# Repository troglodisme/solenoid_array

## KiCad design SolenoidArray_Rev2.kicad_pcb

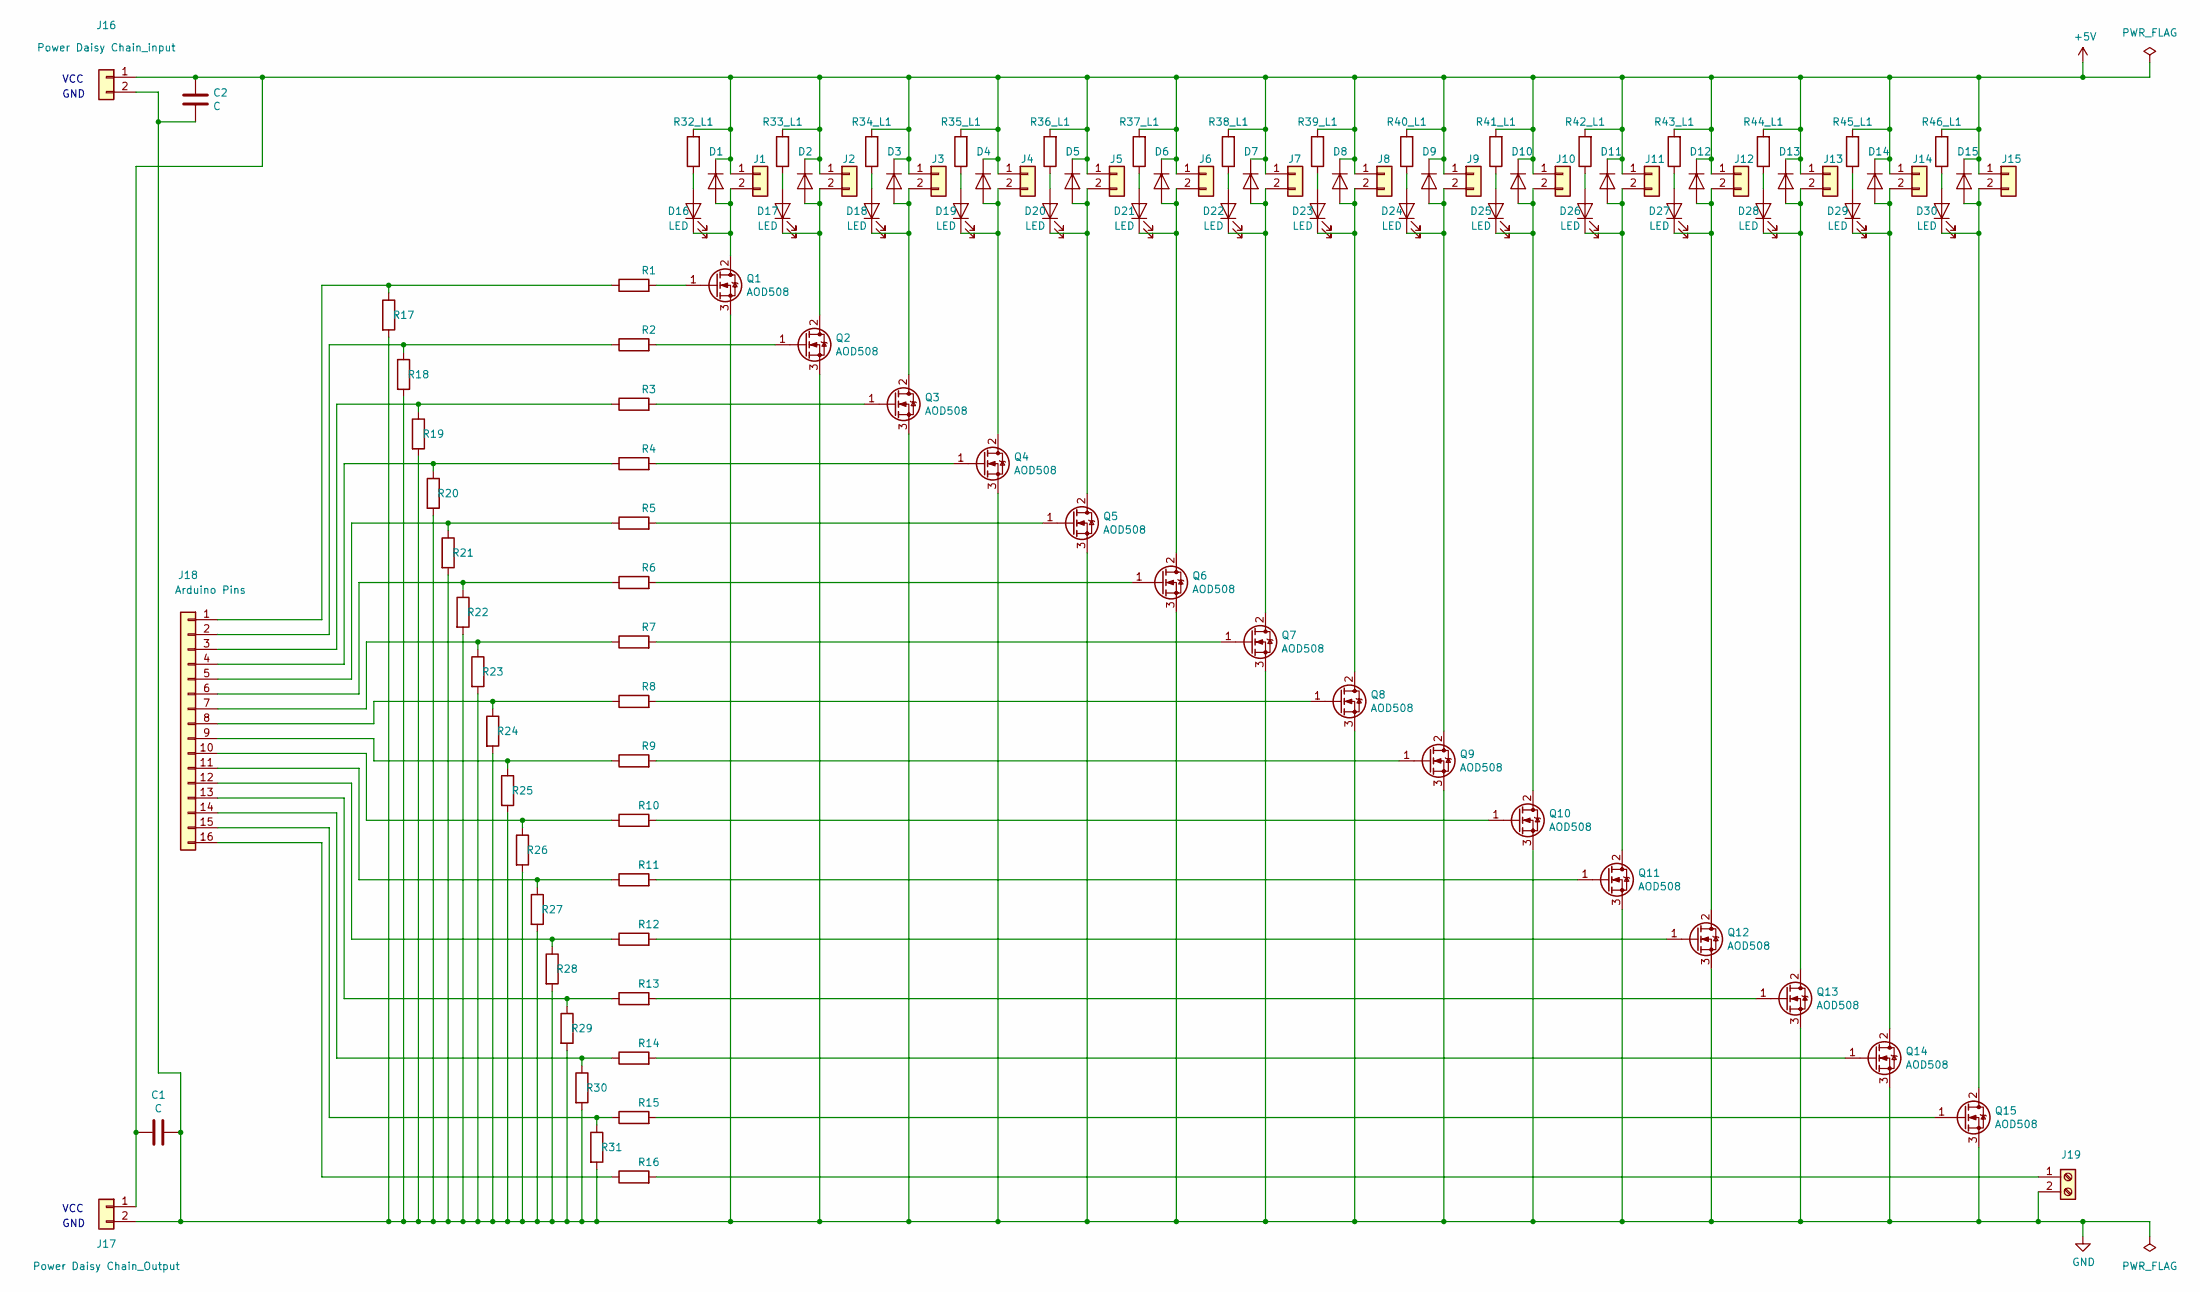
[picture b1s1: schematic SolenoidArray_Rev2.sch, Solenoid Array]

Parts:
C1, C2: C; C_1210_3225Metric_Pad1.42x2.65mm_HandSolder
D1, D2, D3, D4, D5, D6, D7, D8, D9, D10, D11, D12, D13, D14, D15: 1N4004; D_1210_3225Metric_Pad1.42x2.65mm_HandSolder
D16, D17, D18, D19, D20, D21, D22, D23, D24, D25, D26, D27, D28, D29, D30: LED; LED_1210_3225Metric_Pad1.42x2.65mm_HandSolder
J1, J2, J3, J4, J5, J6, J7, J8, J9, J10, J11, J12, J13, J14, J15: Conn_01x02; JST_PH_S2B-PH-K_1x02_P2.00mm_Horizontal
J16: Power Daisy Chain_input; JST_PH_S2B-PH-K_1x02_P2.00mm_Horizontal
J17: Power Daisy Chain_Output; JST_PH_S2B-PH-K_1x02_P2.00mm_Horizontal
J18: Arduino Pins; IDC-Header_2x08_P2.54mm_Vertical
J19: Screw_Terminal_01x02; TerminalBlock_TE_282834-2_1x02_P2.54mm_Horizontal
Q1, Q2, Q3, Q4, Q5, Q6, Q7, Q8, Q9, Q10, Q11, Q12, Q13, Q14, Q15: AOD508; TO252 (DPAK)
R1, R2, R3, R4, R5, R6, R7, R8, R9, R10, R11, R12, R13, R14, R15, R16, R17, R18, R19, R20, R21, R22, R23, R24, R25, R26, R27, R28, R29, R30, R31, R32_L1, R33_L1, R34_L1, R35_L1, R36_L1, R37_L1, R38_L1, R39_L1, R40_L1, R41_L1, R42_L1, R43_L1, R44_L1, R45_L1, R46_L1: R; R_1210_3225Metric_Pad1.42x2.65mm_HandSolder

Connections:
+5V: C1.2, C2.2, D1.1 (K), D2.1 (K), D3.1 (K), D4.1 (K), D5.1 (K), D6.1 (K), D7.1 (K), D8.1 (K), D9.1 (K), D10.1 (K), D11.1 (K), D12.1 (K), D13.1 (K), D14.1 (K), D15.1 (K), J1.1, J2.1, J3.1, J4.1, J5.1, J6.1, J7.1, J8.1, J9.1, J10.1, J11.1, J12.1, J13.1, J14.1, J15.1, J16.1, J17.1, R32_L1.2, R33_L1.2, R34_L1.2, R35_L1.2, R36_L1.2, R37_L1.2, R38_L1.2, R39_L1.2, R40_L1.2, R41_L1.2, R42_L1.2, R43_L1.2, R44_L1.2, R45_L1.2, R46_L1.2
GND: C1.1, C2.1, J16.2, J17.2, J19.2, Q1.3 (S), Q2.3 (S), Q3.3 (S), Q4.3 (S), Q5.3 (S), Q6.3 (S), Q7.3 (S), Q8.3 (S), Q9.3 (S), Q10.3 (S), Q11.3 (S), Q12.3 (S), Q13.3 (S), Q14.3 (S), Q15.3 (S), R17.2, R18.2, R19.2, R20.2, R21.2, R22.2, R23.2, R24.2, R25.2, R26.2, R27.2, R28.2, R29.2, R30.2, R31.2
unnamed: D1.2 (A), D16.1 (K), J1.2, Q1.2 (D)
unnamed: D10.2 (A), D25.1 (K), J10.2, Q10.2 (D)
unnamed: D11.2 (A), D26.1 (K), J11.2, Q11.2 (D)
unnamed: D12.2 (A), D27.1 (K), J12.2, Q12.2 (D)
unnamed: D13.2 (A), D28.1 (K), J13.2, Q13.2 (D)
unnamed: D14.2 (A), D29.1 (K), J14.2, Q14.2 (D)
unnamed: D15.2 (A), D30.1 (K), J15.2, Q15.2 (D)
unnamed: D16.2 (A), R32_L1.1
unnamed: D2.2 (A), D17.1 (K), J2.2, Q2.2 (D)
unnamed: D17.2 (A), R33_L1.1
unnamed: D3.2 (A), D18.1 (K), J3.2, Q3.2 (D)
unnamed: D18.2 (A), R34_L1.1
unnamed: D4.2 (A), D19.1 (K), J4.2, Q4.2 (D)
unnamed: D19.2 (A), R35_L1.1
unnamed: D5.2 (A), D20.1 (K), J5.2, Q5.2 (D)
unnamed: D20.2 (A), R36_L1.1
unnamed: D6.2 (A), D21.1 (K), J6.2, Q6.2 (D)
unnamed: D21.2 (A), R37_L1.1
unnamed: D7.2 (A), D22.1 (K), J7.2, Q7.2 (D)
unnamed: D22.2 (A), R38_L1.1
unnamed: D8.2 (A), D23.1 (K), J8.2, Q8.2 (D)
unnamed: D23.2 (A), R39_L1.1
unnamed: D9.2 (A), D24.1 (K), J9.2, Q9.2 (D)
unnamed: D24.2 (A), R40_L1.1
unnamed: D25.2 (A), R41_L1.1
unnamed: D26.2 (A), R42_L1.1
unnamed: D27.2 (A), R43_L1.1
unnamed: D28.2 (A), R44_L1.1
unnamed: D29.2 (A), R45_L1.1
unnamed: D30.2 (A), R46_L1.1
unnamed: J18.1, R1.1, R17.1
unnamed: J18.2, R2.1, R18.1
unnamed: J18.3, R3.1, R19.1
unnamed: J18.4, R4.1, R20.1
unnamed: J18.5, R5.1, R21.1
unnamed: J18.6, R6.1, R22.1
unnamed: J18.7, R7.1, R23.1
unnamed: J18.8, R8.1, R24.1
unnamed: J18.9, R9.1, R25.1
unnamed: J18.10, R10.1, R26.1
unnamed: J18.11, R11.1, R27.1
unnamed: J18.12, R12.1, R28.1
unnamed: J18.13, R13.1, R29.1
unnamed: J18.14, R14.1, R30.1
unnamed: J18.15, R15.1, R31.1
unnamed: J18.16, R16.1
unnamed: J19.1, R16.2
unnamed: Q1.1 (G), R1.2
unnamed: Q2.1 (G), R2.2
unnamed: Q3.1 (G), R3.2
unnamed: Q4.1 (G), R4.2
unnamed: Q5.1 (G), R5.2
unnamed: Q6.1 (G), R6.2
unnamed: Q7.1 (G), R7.2
unnamed: Q8.1 (G), R8.2
unnamed: Q9.1 (G), R9.2
unnamed: Q10.1 (G), R10.2
unnamed: Q11.1 (G), R11.2
unnamed: Q12.1 (G), R12.2
unnamed: Q13.1 (G), R13.2
unnamed: Q14.1 (G), R14.2
unnamed: Q15.1 (G), R15.2

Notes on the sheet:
GND
VCC

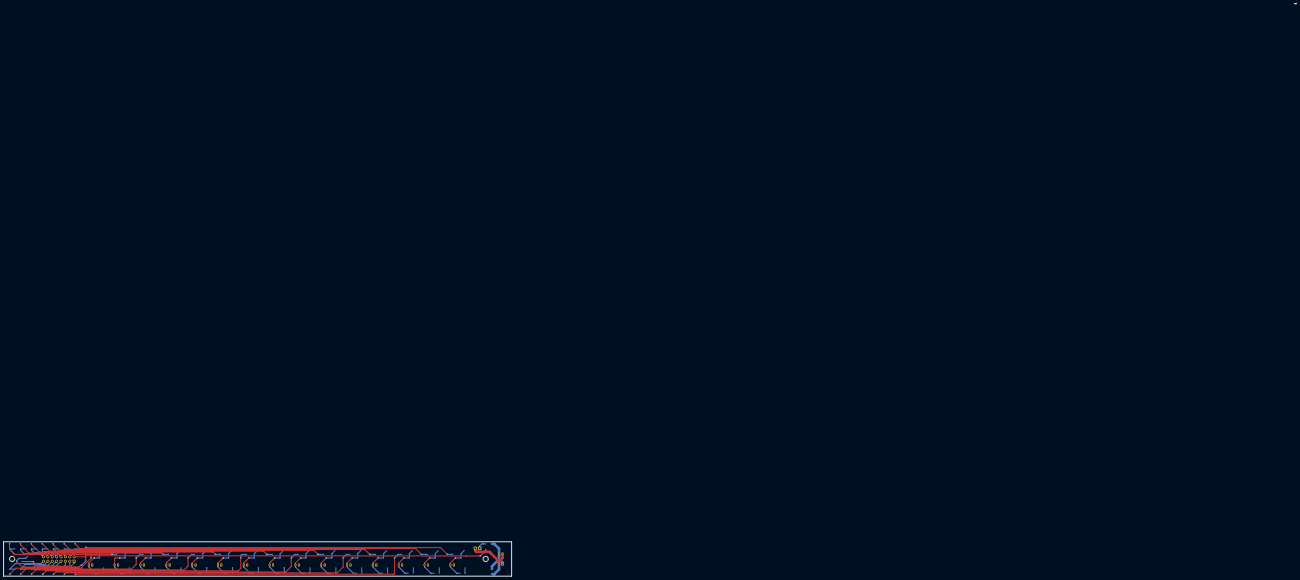
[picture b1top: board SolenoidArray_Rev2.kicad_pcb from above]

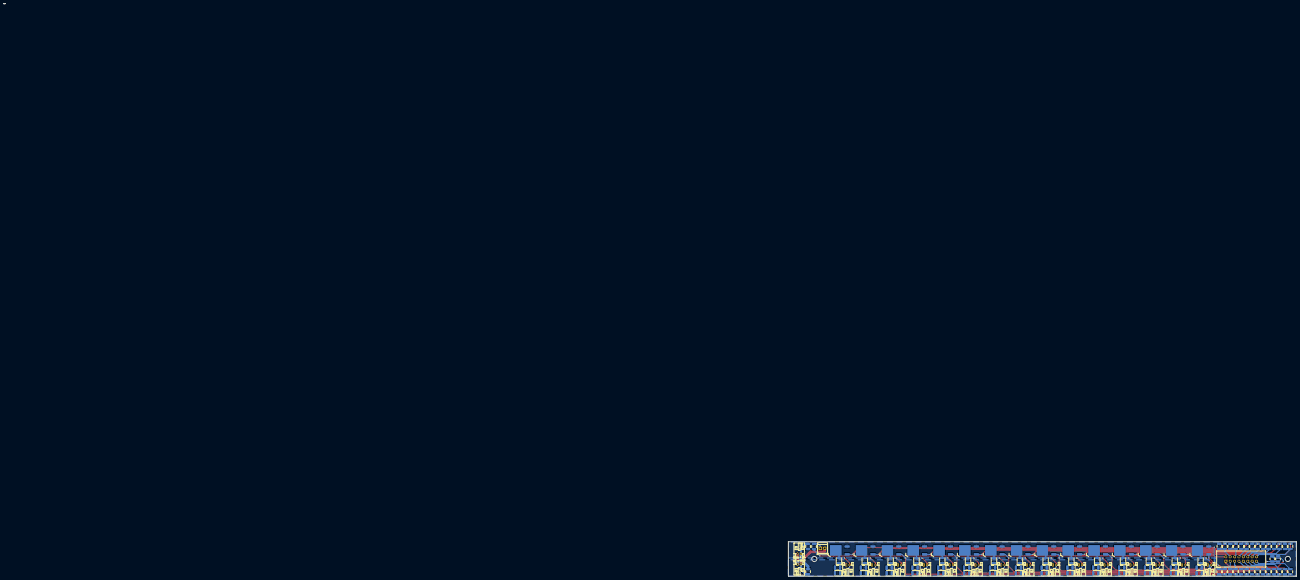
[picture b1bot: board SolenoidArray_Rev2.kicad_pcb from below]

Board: 2 copper layers, 295.0 x 20.0 mm, 112 parts (112 on the bottom side), 64 nets.

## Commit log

2020-05-07 First upload
2020-05-07 Moved right hole to correct position
2020-05-09 Schematic and PCB Rev2
